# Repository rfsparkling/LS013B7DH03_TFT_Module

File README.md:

1.28-inch (diagonal) Memory LCD with Voltage Level Shifter and LDO, in Eagle CAD

Already assambled PCB, validated and it works.

I have assambled PCBs to sell, please contact me about the details!

http://www.sharpmemorylcd.com/1-28-inch-memory-lcd.html

"Sharps 1.28-inch (diagonal) Memory LCD is ideal for digital wristwatches and other small-screen applications, with a 3V input voltage that makes it compatible for operation with a single cell Lithium ion battery. Its high-resolution, dot matrix display delivers smooth graphics and the flexibility to showcase rich custom content.

Overview 
- 1.28 inch 128 x 128 monochrome HR-TFT transflective panel 
- Transmissive mode is available by implemention with backlight. (Transmition ratio is around 0.2%) 
- 128x 128 dot stripe arrangement 
- Display control with serial data signal communication 
- Arbitrary gate line is selectable to data update   
- Internal 1bit memory within the panel for data memory 
- Thin, light and compact module with monolithic technology 
- Super low power consumption TFT panel 
- With FPC (Applicable connector:    Refer to recommended connector on page 21.)  "

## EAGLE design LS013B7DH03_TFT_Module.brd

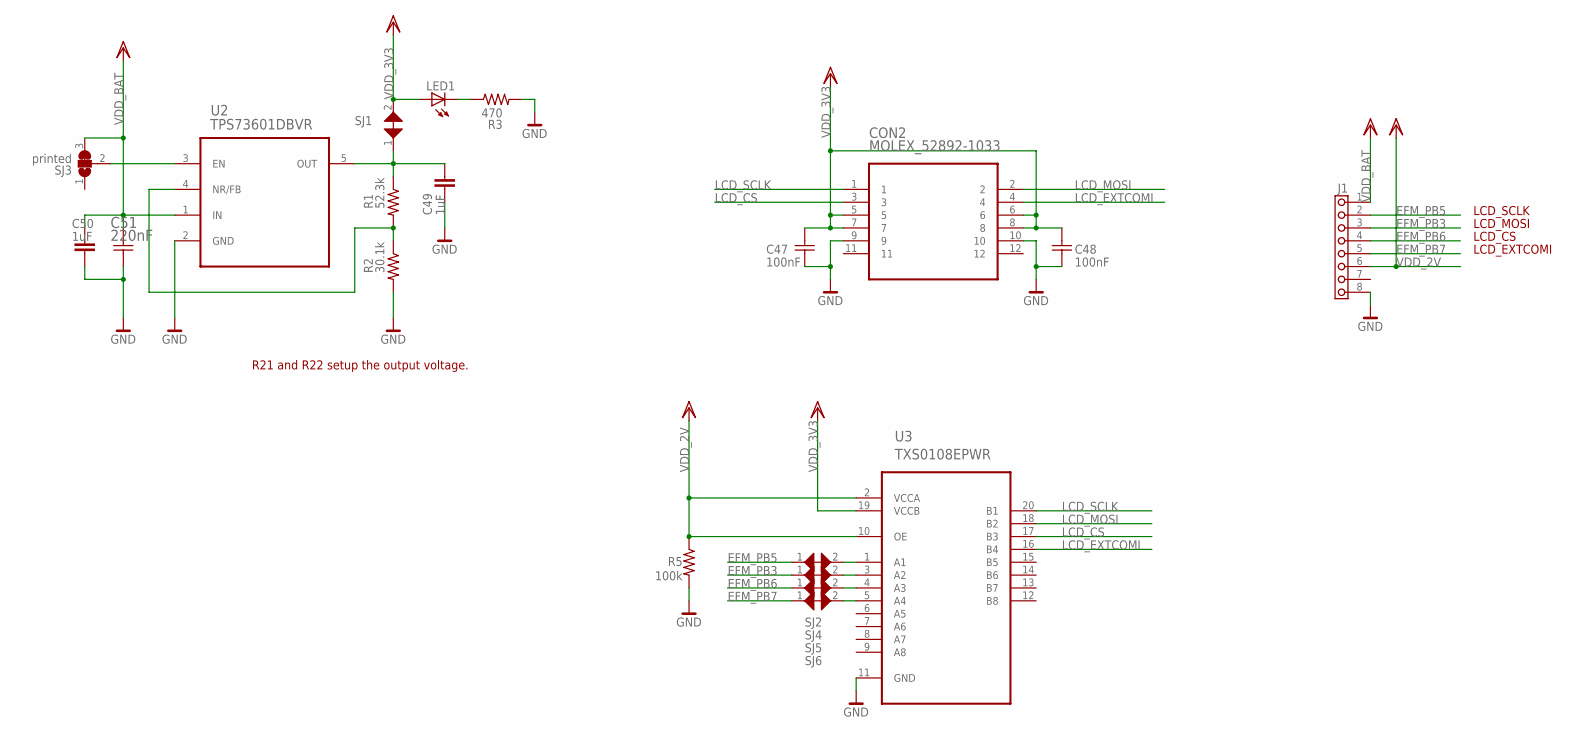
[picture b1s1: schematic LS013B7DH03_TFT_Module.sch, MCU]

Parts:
C47, C48: 100nF; CAPC1005X60N
C49, C50: 1uF; 0603
C51: 220nF; CAPC1005X60N
CON2: MOLEX_52892-1033; MOLEX_52892-1095
J1: PIN8S
LED1: LED0603; LED-0603
R1: 52.3k; R0402
R2: 30.1k; R0402
R3: 470; R0402
R5: 100k; R0402
SJ1, SJ2, SJ4, SJ5, SJ6: printed; JUMPER_SMD_MICRO_SHORT
SJ3: printed; JUMPER_SMD_SJ2A
U2: TPS73601DBVR; SOT95P280X145-5N
U3: TXS0108EPWR; SOP65P640X120-20N

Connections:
EFM_PB3: J1.3, SJ4.1
EFM_PB5: J1.2, SJ2.1
EFM_PB6: J1.4, SJ5.1
EFM_PB7: J1.5, SJ6.1
GND: C47.2 (C2), C48.2 (C2), C49.1, C50.1, C51.2 (C2), CON2.9, CON2.10, J1.8, R2.2, R3.2, R5.2, U2.2 (GND), U3.11 (GND)
LCD_CS: CON2.3, U3.17 (B3)
LCD_EXTCOMI: CON2.4, U3.16 (B4)
LCD_MOSI: CON2.2, U3.18 (B2)
LCD_SCLK: CON2.1, U3.20 (B1)
unnamed: LED1.C, R3.1
unnamed: SJ2.2, U3.1 (A1)
unnamed: SJ4.2, U3.3 (A2)
unnamed: SJ5.2, U3.4 (A3)
unnamed: SJ6.2, U3.5 (A4)
unnamed: C49.2, R1.1, SJ1.1, U2.5 (OUT)
unnamed: R1.2, R2.1, U2.4 (NR/FB)
unnamed: SJ3.2, U2.3 (EN)
VDD_2V: J1.6, R5.1, U3.2 (VCCA), U3.10 (OE)
VDD_3V3: C47.1 (C1), C48.1 (C1), CON2.5, CON2.6, CON2.7, CON2.8, LED1.A, SJ1.2, U3.19 (VCCB)
VDD_BAT: C50.2, C51.1 (C1), J1.1, SJ3.3, U2.1 (IN)

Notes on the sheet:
R21 and R22 setup the output voltage.
LCD_SCLK
LCD_MOSI
LCD_CS
LCD_EXTCOMI

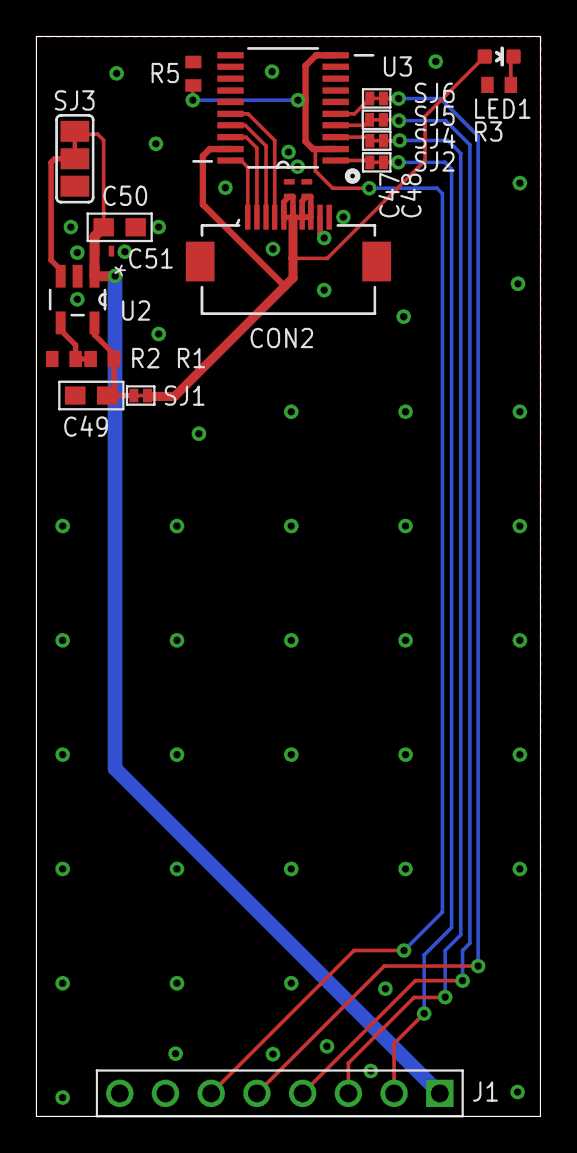
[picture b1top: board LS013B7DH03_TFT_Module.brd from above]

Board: 2 copper layers, 28.0 x 60.0 mm, 20 parts (0 on the bottom side), 20 nets.

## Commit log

2015-12-16 :lollipop: Added .gitattributes & .gitignore files
2015-12-16 adding files
2015-12-16 correction
2015-12-16 adding lic file
